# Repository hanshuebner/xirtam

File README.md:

## Synopsis

xirtam is a an interface device to connect a USB keyboard to a computer with a
matrix keyboard interface, i.e. an 8 bit home computer.

The repository contains the AT90USB1287 firmware source code and KiCAD schematic/PCB
design for the xirtam project.  It is a fork of the [SmallyMouse2](https://www.waitingforfriday.com/?p=827)
project that implements a similar device for realy computer mice.

## Motivation

8 bit home computers interface to their keyboard through a matrix style interface.
The main CPU periodically scans the keyboard matrix for key presses converts them to
characters or control information as required.  This is in contrast to more modern
machines, where a separate microcontroller performs the keyboard scanning task and
interfaces to the main CPU using a serial interface.

Being able to use an USB interface with an 8 bit home computer is often desireable
because of the bad quality that home computer keyboards typically have. Some don't
even have physical keys, but most use cheap mechanical switches.  Furthermore, the
keyboard is always integrated into the system unit, and a detachable keyboard is
much desireable.

## Implementation

Interfacing a modern keyboard to a computer with a matrix interface is slightly
tricky because of the way how the scanning is typically implemented.  The keyboard
is organized as a matrix of switches, with each switch connecting a particular pair
of a vertical and horizontal line of the matrix.  It does so by sending a high 
signal to one of the row lines of the matrix, and then reading back the
value sent by the keyboard on the column lines.  For each key pressed in the
particular row, the respective column bit will be high.

The scanning of the keyboard is a rapid process, with little time between when the
row was selected and the column being read.  Typically, there will only be a few
hundred nanoseconds between when the CPU selects a row and when it reads back the
column data.  Hence, software based solutions to emulate a keyboard matrix, while
they exist, require a very fast microcontroller or additional hardware or software
running on the micro to work.

xirtam approaches the timing problem by using a matrix switch chip that works
the same way as a physical keyboard.  The physical switches of the keyboard are
replaced by semiconductor switches inside of the chip which can be controlled
by a host interface.  When one of the switches is turned on by the host, it
connects the row and column at its intersection until the host turns if off again.
Hence, the scanning of the keyboard by the home computer can be done at arbitrary
rate, like with a physical keyboard.

Matrix switch chips are used in video and
audio crossbar applications and have been around for a long time.  They are
available in various configurations and sizes and are reasonably priced.  The
chip chosen for xirtam is the [MT093](https://www.microsemi.com/document-portal/doc_download/127014-mt093-datasheet-sept11).  
It was developed by Zarlink (now Microchip) and provides for 96 switches in an 
8x12 configuration.  It provides an easy to use interface for control, 
allowing the microcontroller to address one of the switches on a parallel address
bus and sending the desired switch state on a separate data bit.

xirtam supports both JTAG and USB bootloader programming.  The AT90USB1287 
is pre-programmed by Atmel with the (FLIP) DFU bootloader; this bootloader is 
recognised by Atmel Studio as a programming device and can be used to flash the 
firmware to the board.

## Installation

Note: This is an Atmel Studio 7 project that can be loaded and compiled by the IDE

Please see http://www.waitingforfriday.com/?p=827 for detailed documentation about SmallyMouse2

## Authors

SmallyMouse2 was written and is maintained by Simon Inns.  It was adapted to xirtam
by Hans Hübner.

## License (Software)

    SmallyMouse2 is free software: you can redistribute it and/or modify
    it under the terms of the GNU General Public License as published by
    the Free Software Foundation, either version 3 of the License, or
    (at your option) any later version.

    SmallyMouse2 is distributed in the hope that it will be useful,
    but WITHOUT ANY WARRANTY; without even the implied warranty of
    MERCHANTABILITY or FITNESS FOR A PARTICULAR PURPOSE.  See the
    GNU General Public License for more details.

    You should have received a copy of the GNU General Public License
    along with SmallyMouse2. If not, see <http://www.gnu.org/licenses/>.

## License (Hardware)

Both the schematic and the PCB design of xirtam (i.e. the KiCAD project and files)
are covered by a Creative Commons license; as with the software you are welcome 
(and encouraged!) to extend, re-spin and otherwise use and modify the design as 
allowed by the license.  However; under the terms of the Attribution-ShareAlike 
4.0 International (CC BY-SA 4.0) license you are required to release your design 
5.(or redesign) under the same license.  For details of the licensing requirements 
6.please see <https://creativecommons.org/licenses/by-sa/4.0/>

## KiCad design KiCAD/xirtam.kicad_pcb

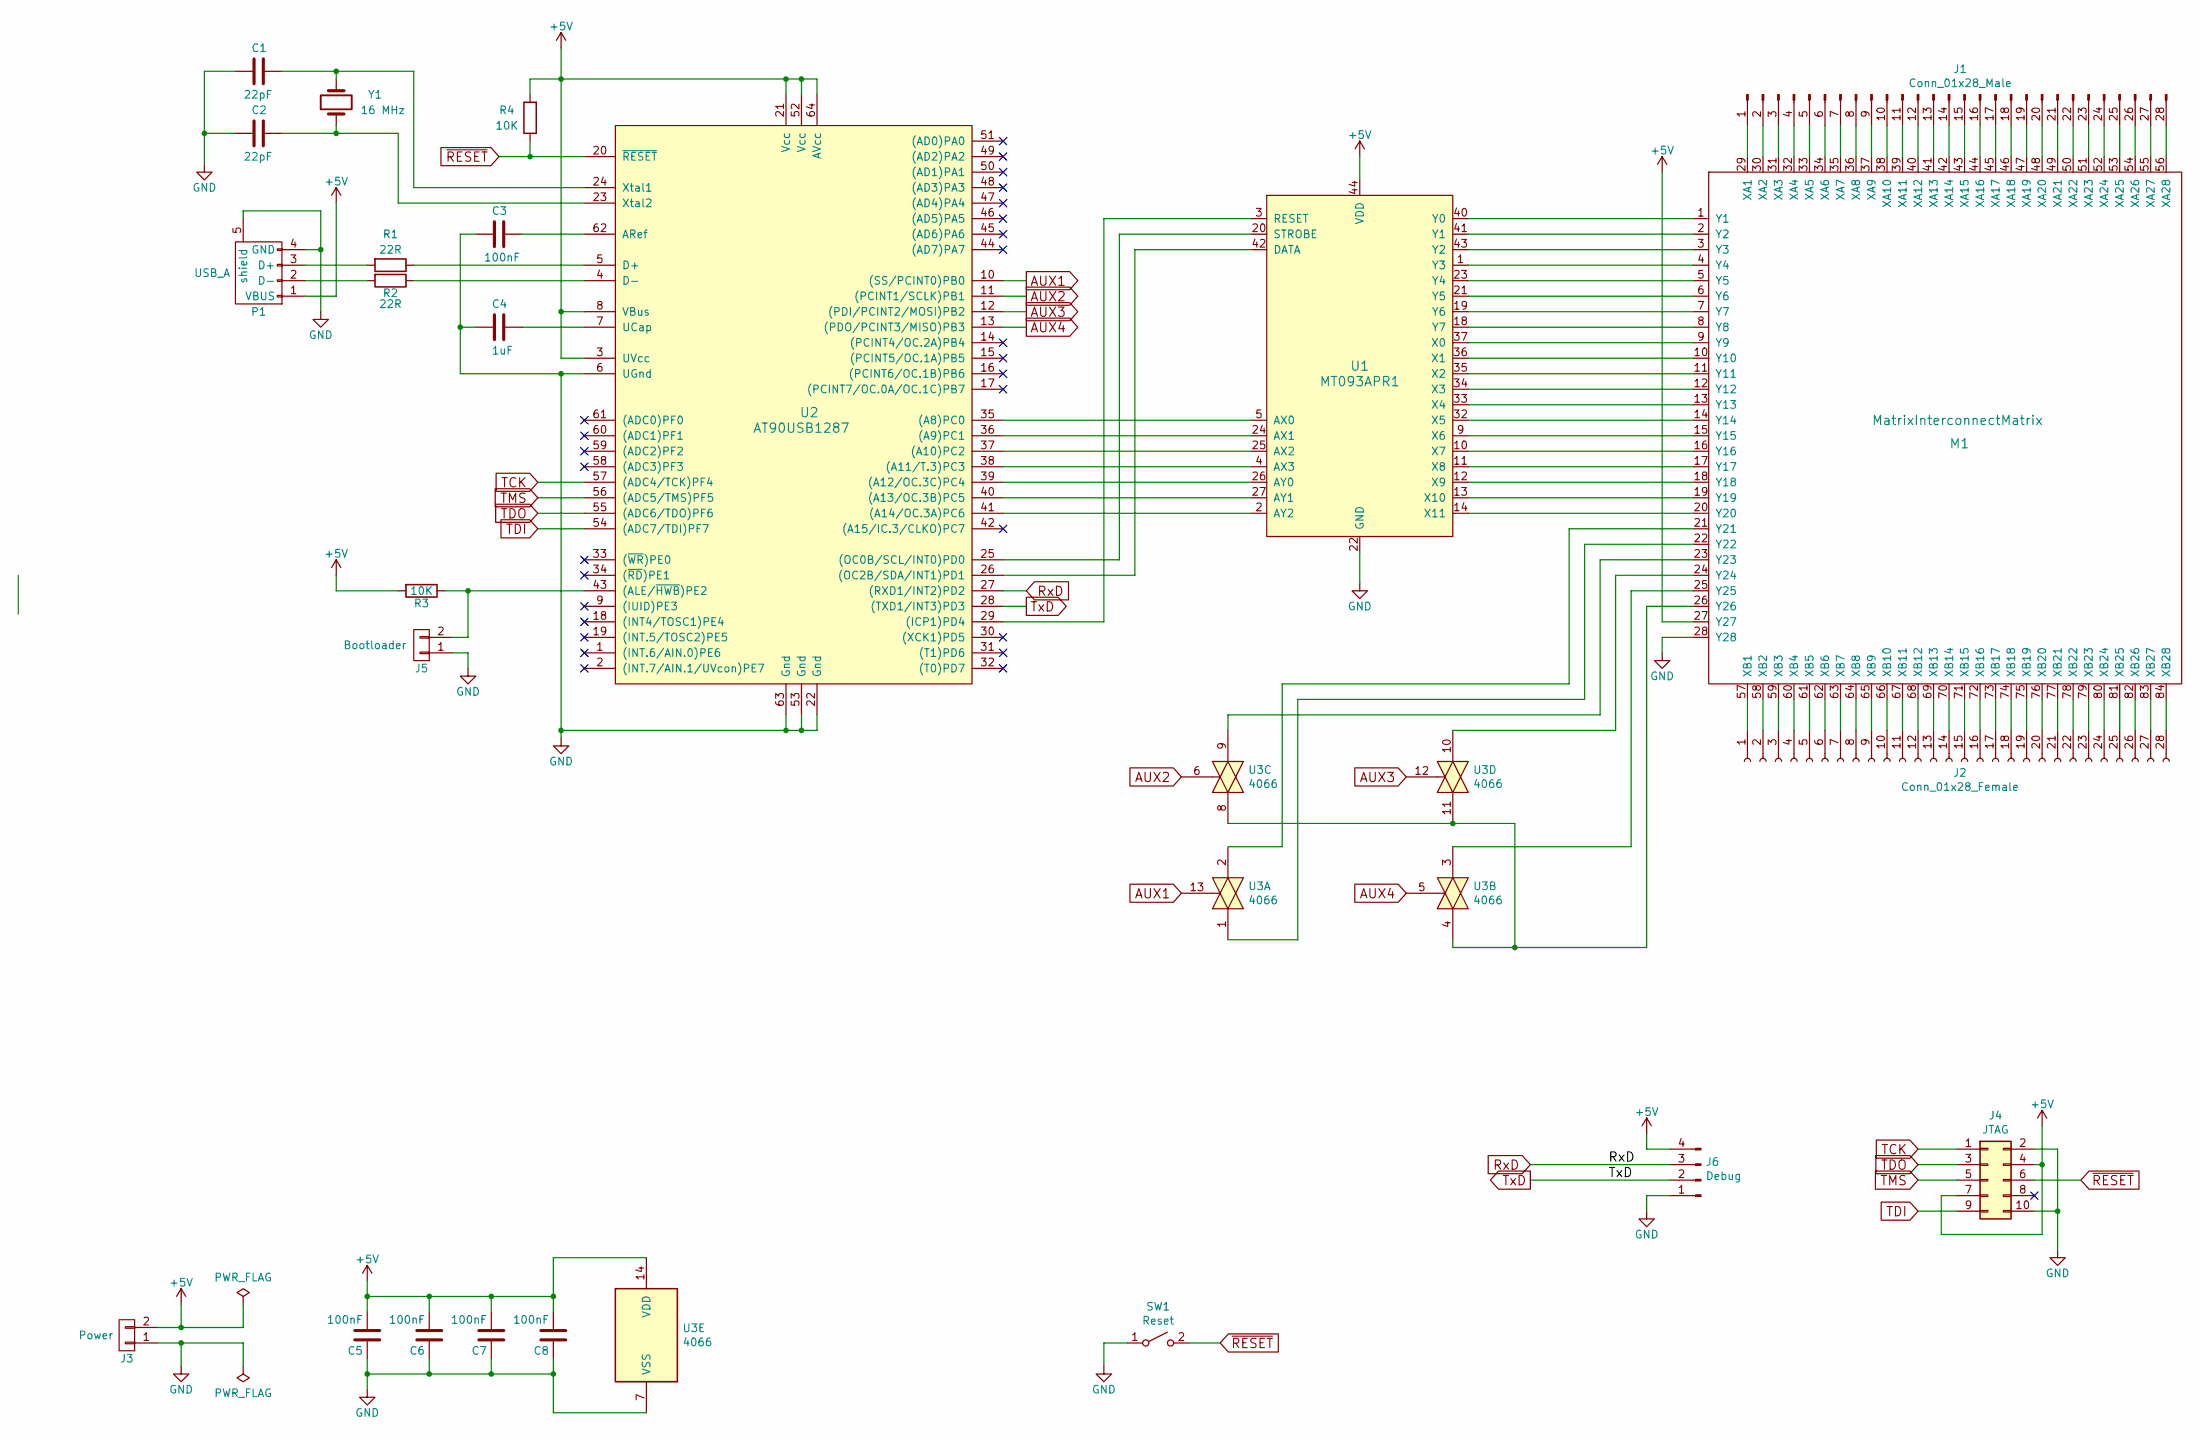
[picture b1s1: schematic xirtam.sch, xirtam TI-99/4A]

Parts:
C1, C2: 22pF; C_0603_1608Metric_Pad1.05x0.95mm_HandSolder
C3, C5, C6, C7, C8: 100nF; C_0603_1608Metric_Pad1.05x0.95mm_HandSolder
C4: 1uF; C_0603_1608Metric_Pad1.05x0.95mm_HandSolder
J1: Conn_01x28_Male; PinHeader_1x28_P2.54mm_Horizontal
J2: Conn_01x28_Female; PinSocket_1x28_P2.54mm_Horizontal
J3: Power; PinHeader_1x02_P2.54mm_Horizontal
J4: JTAG; IDC-Header_2x05_P2.54mm_Horizontal
J5: Bootloader; PinHeader_1x02_P2.54mm_Horizontal
J6: Debug; PinHeader_1x04_P2.54mm_Horizontal
M1: MatrixInterconnectMatrix; matrixinterconnectmatrix
P1: USB_A; Amphenol_87583-2010BLF
R1, R2: 22R; R_0603_1608Metric_Pad1.05x0.95mm_HandSolder
R3, R4: 10K; R_0603_1608Metric_Pad1.05x0.95mm_HandSolder
SW1: Reset; SW_SPST_FSMSM
U1: MT093APR1; PLCC-44
U2: AT90USB1287; TQFP-64_14x14mm_Pitch0.8mm
U3: 4066; SO-14_5.3x10.2mm_P1.27mm
Y1: 16 MHz; Crystal_SMD_5032-2pin_5.0x3.2mm_HandSoldering

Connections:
+5V: C5.2, C6.2, C7.2, C8.2, J3.2, J4.4, J4.7, J6.4, M1.27 (Y27), P1.1 (VBUS), R3.2, R4.2, U1.44 (VDD), U2.3 (UVcc), U2.8 (VBus), U2.21 (Vcc), U2.52 (Vcc), U2.64 (AVcc), U3.14 (VDD)
AUX1: U2.10 ((SS/PCINT0)PB0), U3.13
AUX2: U2.11 ((PCINT1/SCLK)PB1), U3.6
AUX3: U2.12 ((PDI/PCINT2/MOSI)PB2), U3.12
AUX4: U2.13 ((PDO/PCINT3/MISO)PB3), U3.5
GND: C1.2, C2.2, C3.2, C4.2, C5.1, C6.1, C7.1, C8.1, J3.1, J4.2, J4.10, J5.1, J6.1, M1.28 (Y28), P1.4 (GND), P1.5 (shield), SW1.1 (A), U1.22 (GND), U2.6 (UGnd), U2.22 (Gnd), U2.53 (Gnd), U2.63 (Gnd), U3.7 (VSS)
unnamed: C1.1, U2.24 (Xtal1), Y1.2
unnamed: C2.1, U2.23 (Xtal2), Y1.1
unnamed: C3.1, U2.62 (ARef)
unnamed: C4.1, U2.7 (UCap)
unnamed: J1.1, M1.29 (XA1)
unnamed: J1.2, M1.30 (XA2)
unnamed: J1.3, M1.31 (XA3)
unnamed: J1.4, M1.32 (XA4)
unnamed: J1.5, M1.33 (XA5)
unnamed: J1.6, M1.34 (XA6)
unnamed: J1.7, M1.35 (XA7)
unnamed: J1.8, M1.36 (XA8)
unnamed: J1.9, M1.37 (XA9)
unnamed: J1.10, M1.38 (XA10)
unnamed: J1.11, M1.39 (XA11)
unnamed: J1.12, M1.40 (XA12)
unnamed: J1.13, M1.41 (XA13)
unnamed: J1.14, M1.42 (XA14)
unnamed: J1.15, M1.43 (XA15)
unnamed: J1.16, M1.44 (XA16)
unnamed: J1.17, M1.45 (XA17)
unnamed: J1.18, M1.46 (XA18)
unnamed: J1.19, M1.47 (XA19)
unnamed: J1.20, M1.48 (XA20)
unnamed: J1.21, M1.49 (XA21)
unnamed: J1.22, M1.50 (XA22)
unnamed: J1.23, M1.51 (XA23)
unnamed: J1.24, M1.52 (XA24)
unnamed: J1.25, M1.53 (XA25)
unnamed: J1.26, M1.54 (XA26)
unnamed: J1.27, M1.55 (XA27)
unnamed: J1.28, M1.56 (XA28)
unnamed: J2.1, M1.57 (XB1)
unnamed: J2.2, M1.58 (XB2)
unnamed: J2.3, M1.59 (XB3)
unnamed: J2.4, M1.60 (XB4)
unnamed: J2.5, M1.61 (XB5)
unnamed: J2.6, M1.62 (XB6)
unnamed: J2.7, M1.63 (XB7)
unnamed: J2.8, M1.64 (XB8)
unnamed: J2.9, M1.65 (XB9)
unnamed: J2.10, M1.66 (XB10)
unnamed: J2.11, M1.67 (XB11)
unnamed: J2.12, M1.68 (XB12)
unnamed: J2.13, M1.69 (XB13)
unnamed: J2.14, M1.70 (XB14)
unnamed: J2.15, M1.71 (XB15)
unnamed: J2.16, M1.72 (XB16)
unnamed: J2.17, M1.73 (XB17)
unnamed: J2.18, M1.74 (XB18)
unnamed: J2.19, M1.75 (XB19)
unnamed: J2.20, M1.76 (XB20)
unnamed: J2.21, M1.77 (XB21)
unnamed: J2.22, M1.78 (XB22)
unnamed: J2.23, M1.79 (XB23)
unnamed: J2.24, M1.80 (XB24)
unnamed: J2.25, M1.81 (XB25)
unnamed: J2.26, M1.82 (XB26)
unnamed: J2.27, M1.83 (XB27)
unnamed: J2.28, M1.84 (XB28)
unnamed: J5.2, R3.1, U2.43 ((ALE/~HWB~)PE2)
unnamed: M1.1 (Y1), U1.40 (Y0)
unnamed: M1.2 (Y2), U1.41 (Y1)
unnamed: M1.3 (Y3), U1.43 (Y2)
unnamed: M1.4 (Y4), U1.1 (Y3)
unnamed: M1.5 (Y5), U1.23 (Y4)
unnamed: M1.6 (Y6), U1.21 (Y5)
unnamed: M1.7 (Y7), U1.19 (Y6)
unnamed: M1.8 (Y8), U1.18 (Y7)
unnamed: M1.9 (Y9), U1.37 (X0)
unnamed: M1.10 (Y10), U1.36 (X1)
unnamed: M1.11 (Y11), U1.35 (X2)
unnamed: M1.12 (Y12), U1.34 (X3)
unnamed: M1.13 (Y13), U1.33 (X4)
unnamed: M1.14 (Y14), U1.32 (X5)
unnamed: M1.15 (Y15), U1.9 (X6)
unnamed: M1.16 (Y16), U1.10 (X7)
unnamed: M1.17 (Y17), U1.11 (X8)
unnamed: M1.18 (Y18), U1.12 (X9)
unnamed: M1.19 (Y19), U1.13 (X10)
unnamed: M1.20 (Y20), U1.14 (X11)
unnamed: M1.21 (Y21), U3.2
unnamed: M1.22 (Y22), U3.1
unnamed: M1.23 (Y23), U3.9
unnamed: M1.24 (Y24), U3.10
unnamed: M1.25 (Y25), U3.3
unnamed: M1.26 (Y26), U3.4, U3.8, U3.11
unnamed: P1.2 (D-), R2.2
unnamed: P1.3 (D+), R1.2
unnamed: R1.1, U2.5 (D+)
unnamed: R2.1, U2.4 (D-)
unnamed: U1.2 (AY2), U2.41 ((A14/OC.3A)PC6)
unnamed: U1.3 (RESET), U2.29 ((ICP1)PD4)
unnamed: U1.4 (AX3), U2.38 ((A11/T.3)PC3)
unnamed: U1.5 (AX0), U2.35 ((A8)PC0)
unnamed: U1.20 (STROBE), U2.25 ((OC0B/SCL/INT0)PD0)
unnamed: U1.24 (AX1), U2.36 ((A9)PC1)
unnamed: U1.25 (AX2), U2.37 ((A10)PC2)
unnamed: U1.26 (AY0), U2.39 ((A12/OC.3C)PC4)
unnamed: U1.27 (AY1), U2.40 ((A13/OC.3B)PC5)
unnamed: U1.42 (DATA), U2.26 ((OC2B/SDA/INT1)PD1)
RxD: J6.3, U2.27 ((RXD1/INT2)PD2)
TCK: J4.1, U2.57 ((ADC4/TCK)PF4)
TDI: J4.9, U2.54 ((ADC7/TDI)PF7)
TDO: J4.3, U2.55 ((ADC6/TDO)PF6)
TMS: J4.5, U2.56 ((ADC5/TMS)PF5)
TxD: J6.2, U2.28 ((TXD1/INT3)PD3)
~RESET: J4.6, R4.1, SW1.2 (B), U2.20 (~RESET)

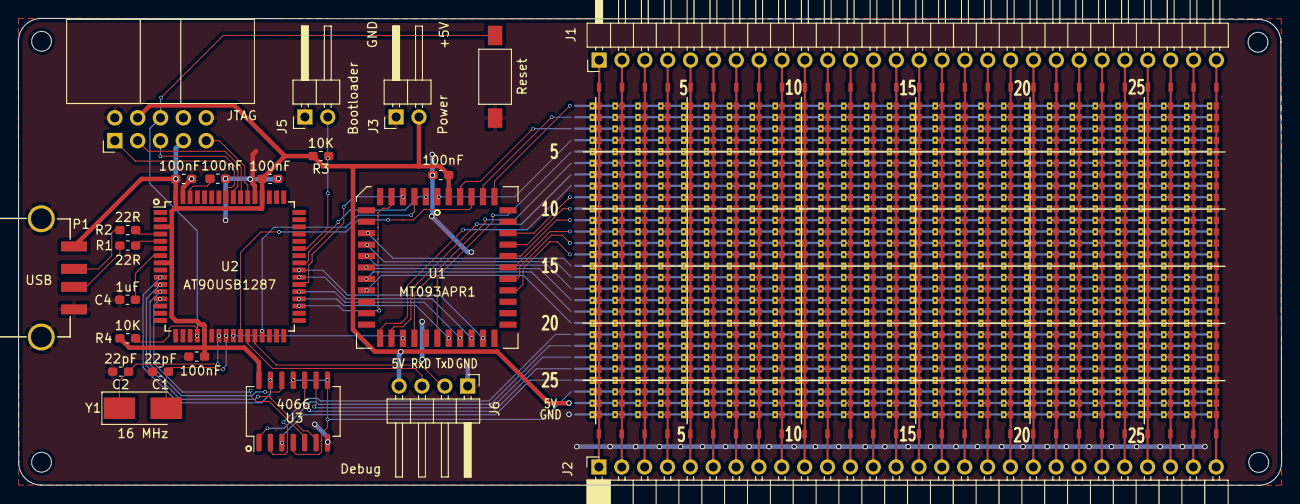
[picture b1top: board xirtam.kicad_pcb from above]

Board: 2 copper layers, 140.3 x 51.9 mm, 25 parts (0 on the bottom side), 114 nets.

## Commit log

2021-04-28 Adapt README to xirtam
2021-05-13 Complete layout
2021-05-14 Fix typo
2021-05-14 Remove backup file
2021-05-14 Remove SmallyMouse2 products
2021-07-27 Add LUFA as of today
2021-07-27 Switch to HID keyboard reading, remove mouse code
2021-07-27 Ignore hex/elf files
2021-07-27 Add keyboard matrix diagram Excel sheet
2021-07-28 Missing lufa files
2021-07-28 Add usb_hid_keys.h and clean up
2021-07-28 Add in-line connector layout to PCB, no routing
2021-07-28 Reindent
2021-07-29 Add serial port, fix bugs, make SmallyMouse2 compatible
2021-07-29 Decodes USB to matrix address
2021-07-29 Clean up and debug
2021-07-29 Tweak comment
2021-07-29 Use LUFA's HID host driver
2021-07-29 Map function / shifted keys
2021-07-30 Excel tweaks
2021-07-31 New PCB layout
2021-08-01 Fix incorrect mapping for left arrow/backspace
2021-08-02 New layout, updated schematic
2021-08-02 Fix formatting for printing

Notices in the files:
KiCAD/xirtam.kicad_pcb:
(c) 2021 Hans Hübner
License: Attribution-ShareAlike 4.0 International (CC BY-SA 4.0)
© Hans Hübner
KiCAD/xirtam.sch:
© 2021 Hans Hübner
